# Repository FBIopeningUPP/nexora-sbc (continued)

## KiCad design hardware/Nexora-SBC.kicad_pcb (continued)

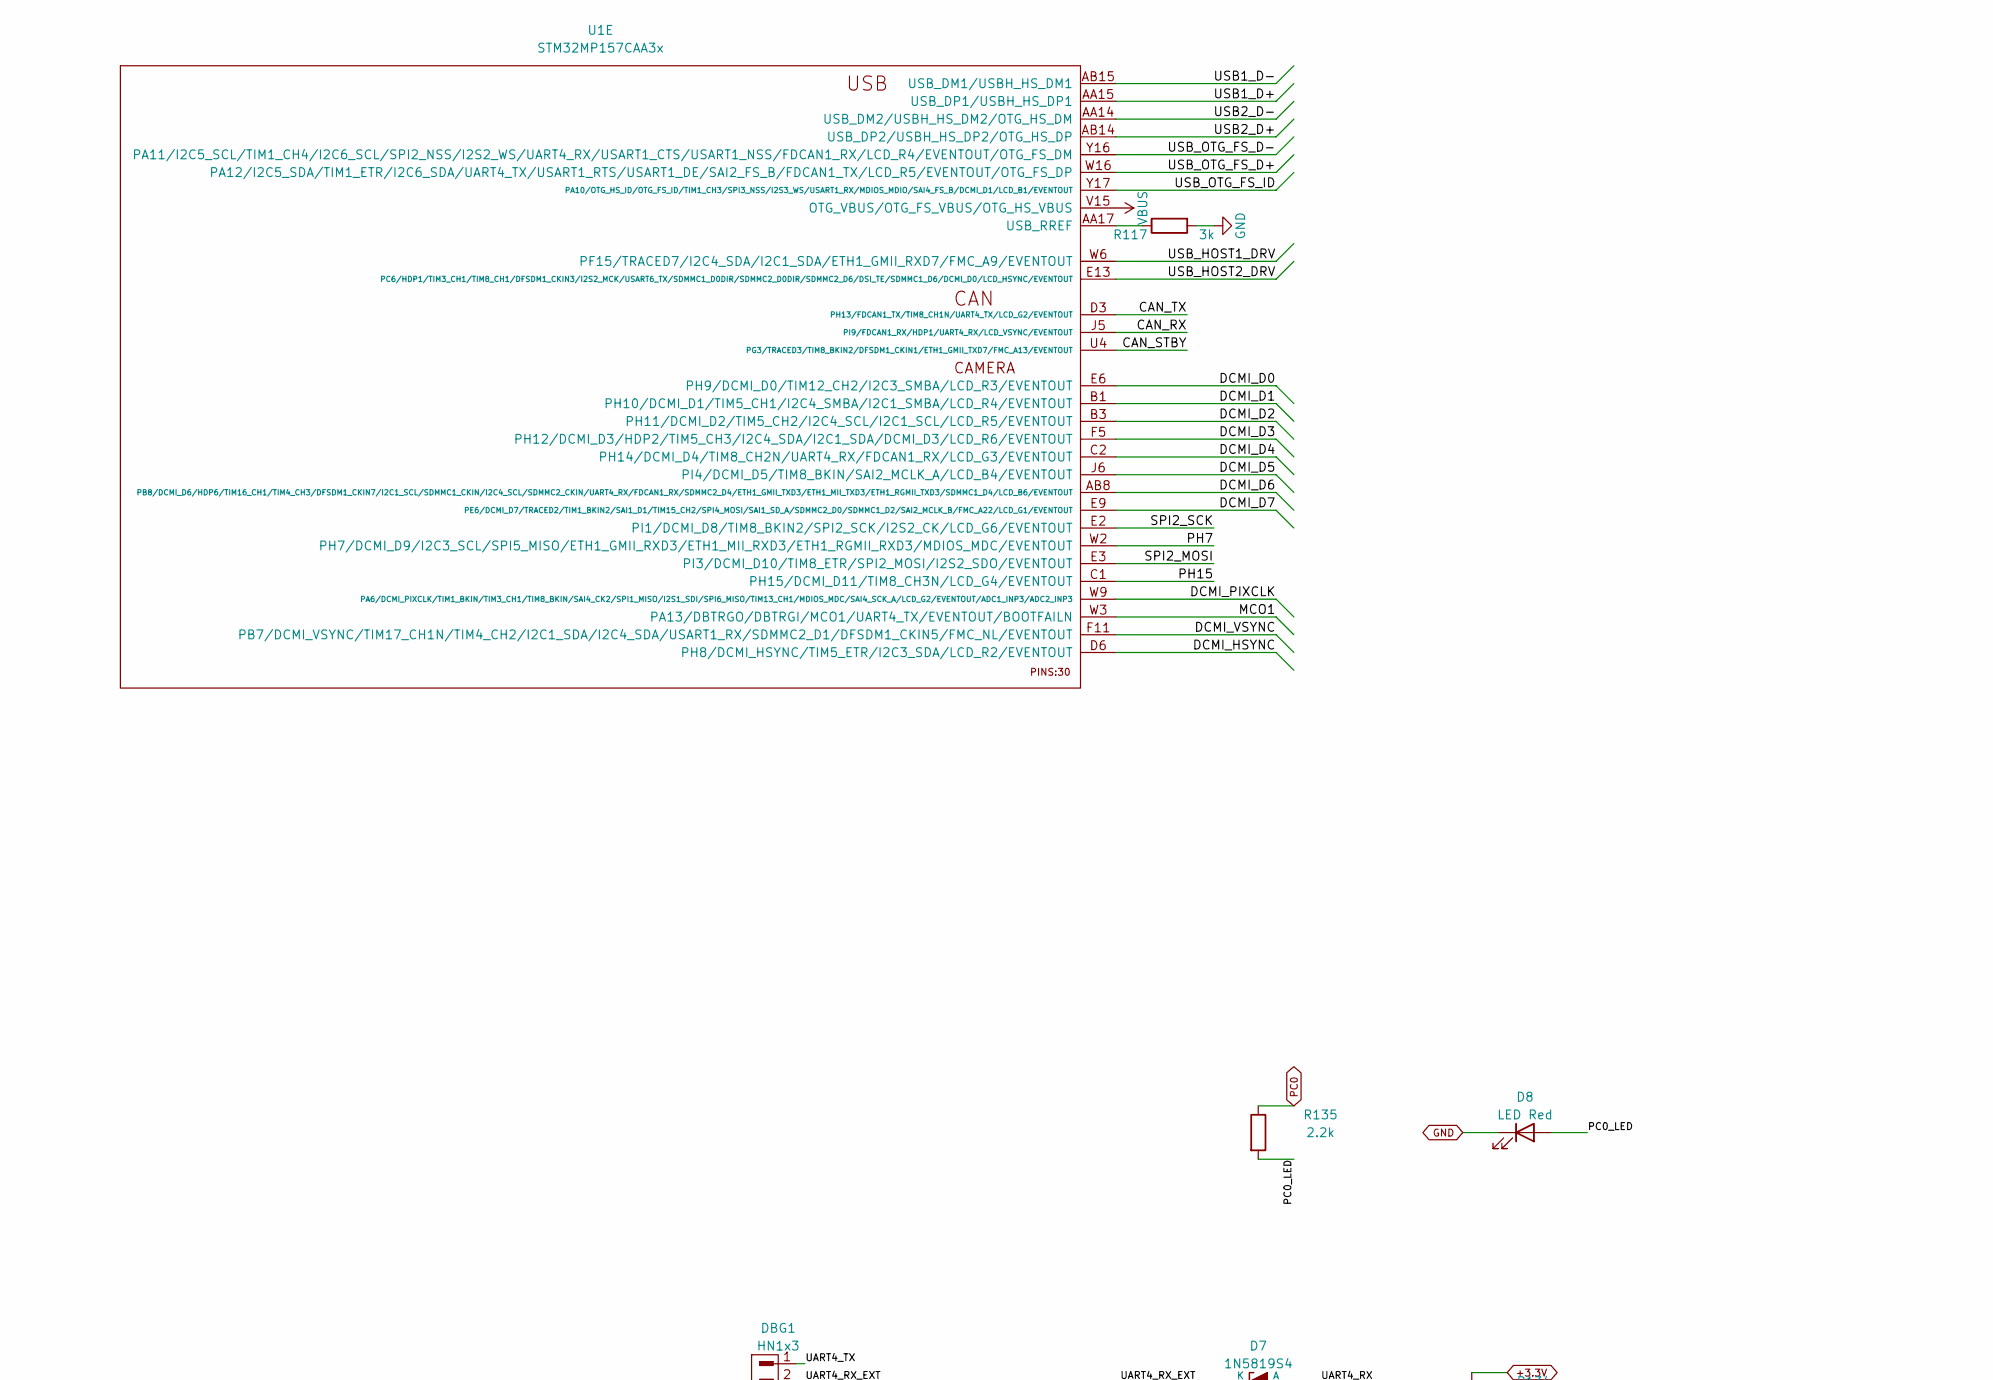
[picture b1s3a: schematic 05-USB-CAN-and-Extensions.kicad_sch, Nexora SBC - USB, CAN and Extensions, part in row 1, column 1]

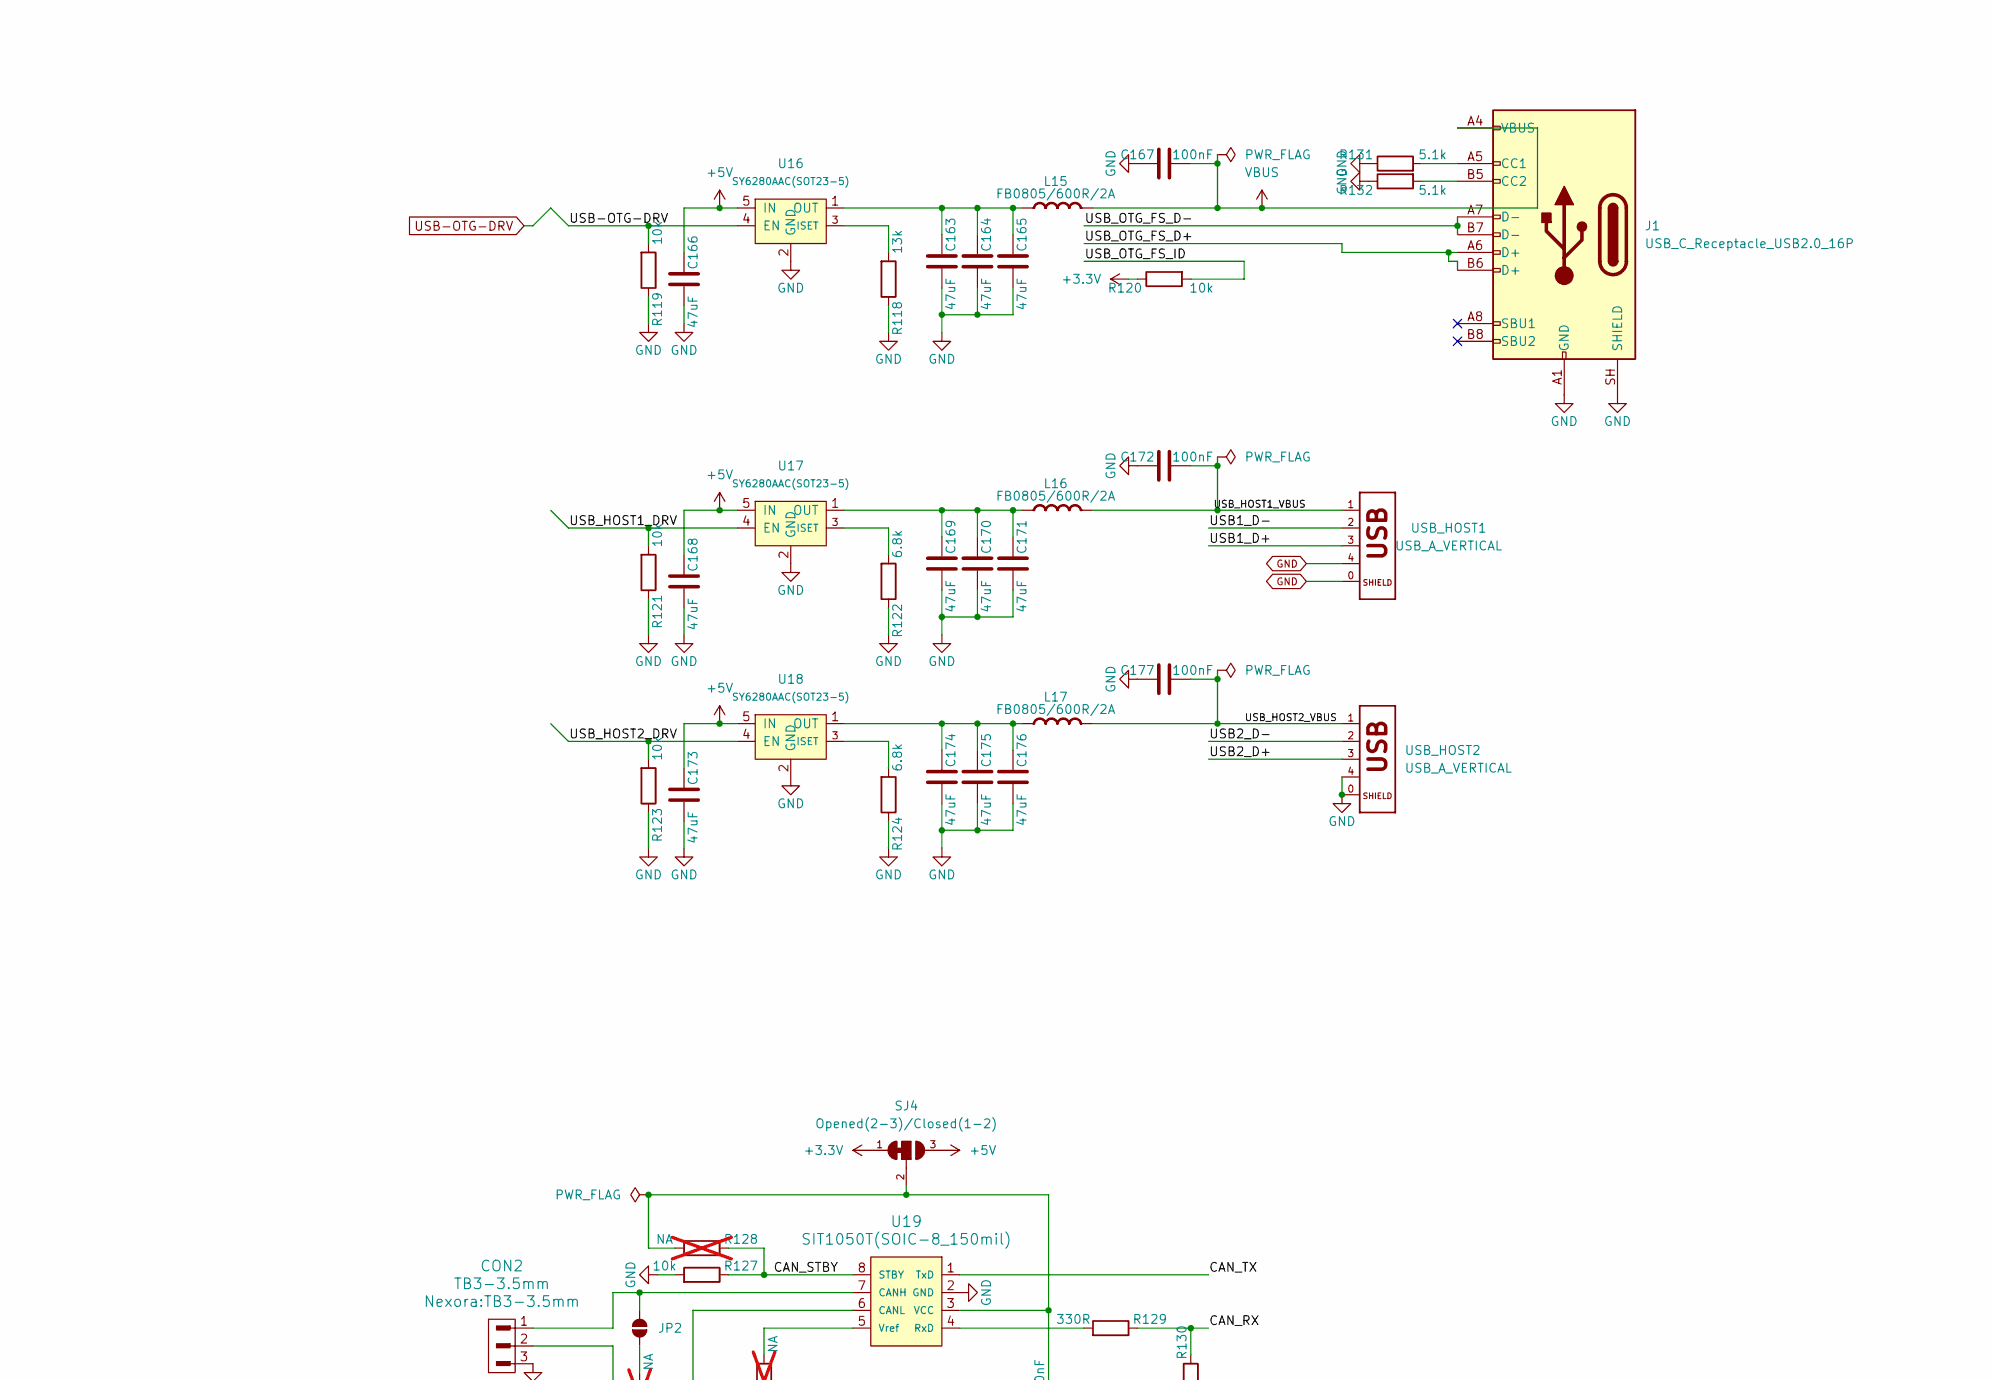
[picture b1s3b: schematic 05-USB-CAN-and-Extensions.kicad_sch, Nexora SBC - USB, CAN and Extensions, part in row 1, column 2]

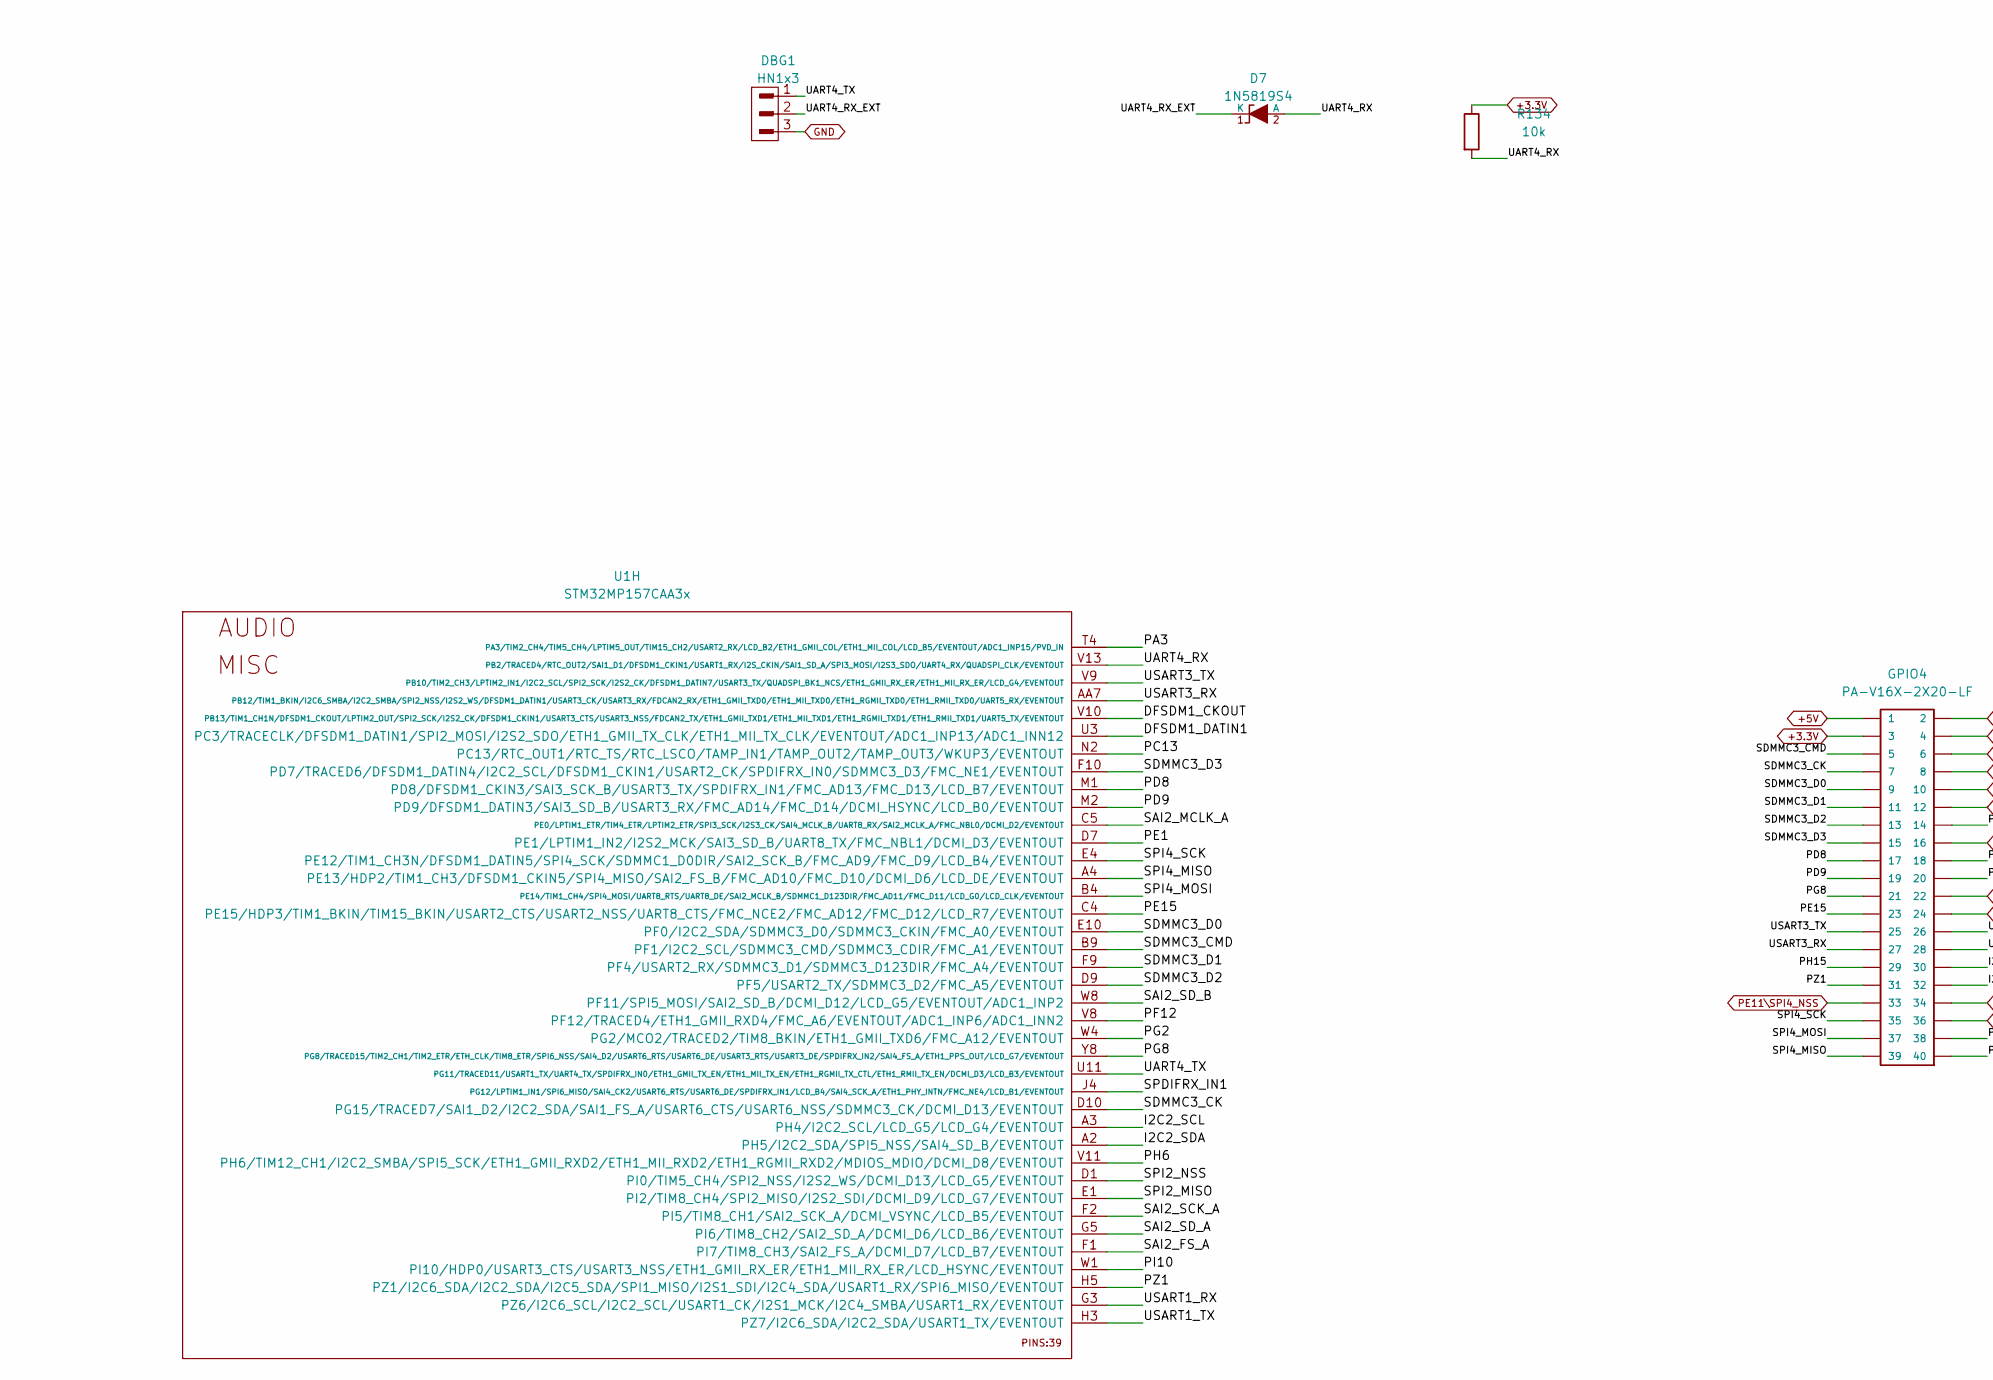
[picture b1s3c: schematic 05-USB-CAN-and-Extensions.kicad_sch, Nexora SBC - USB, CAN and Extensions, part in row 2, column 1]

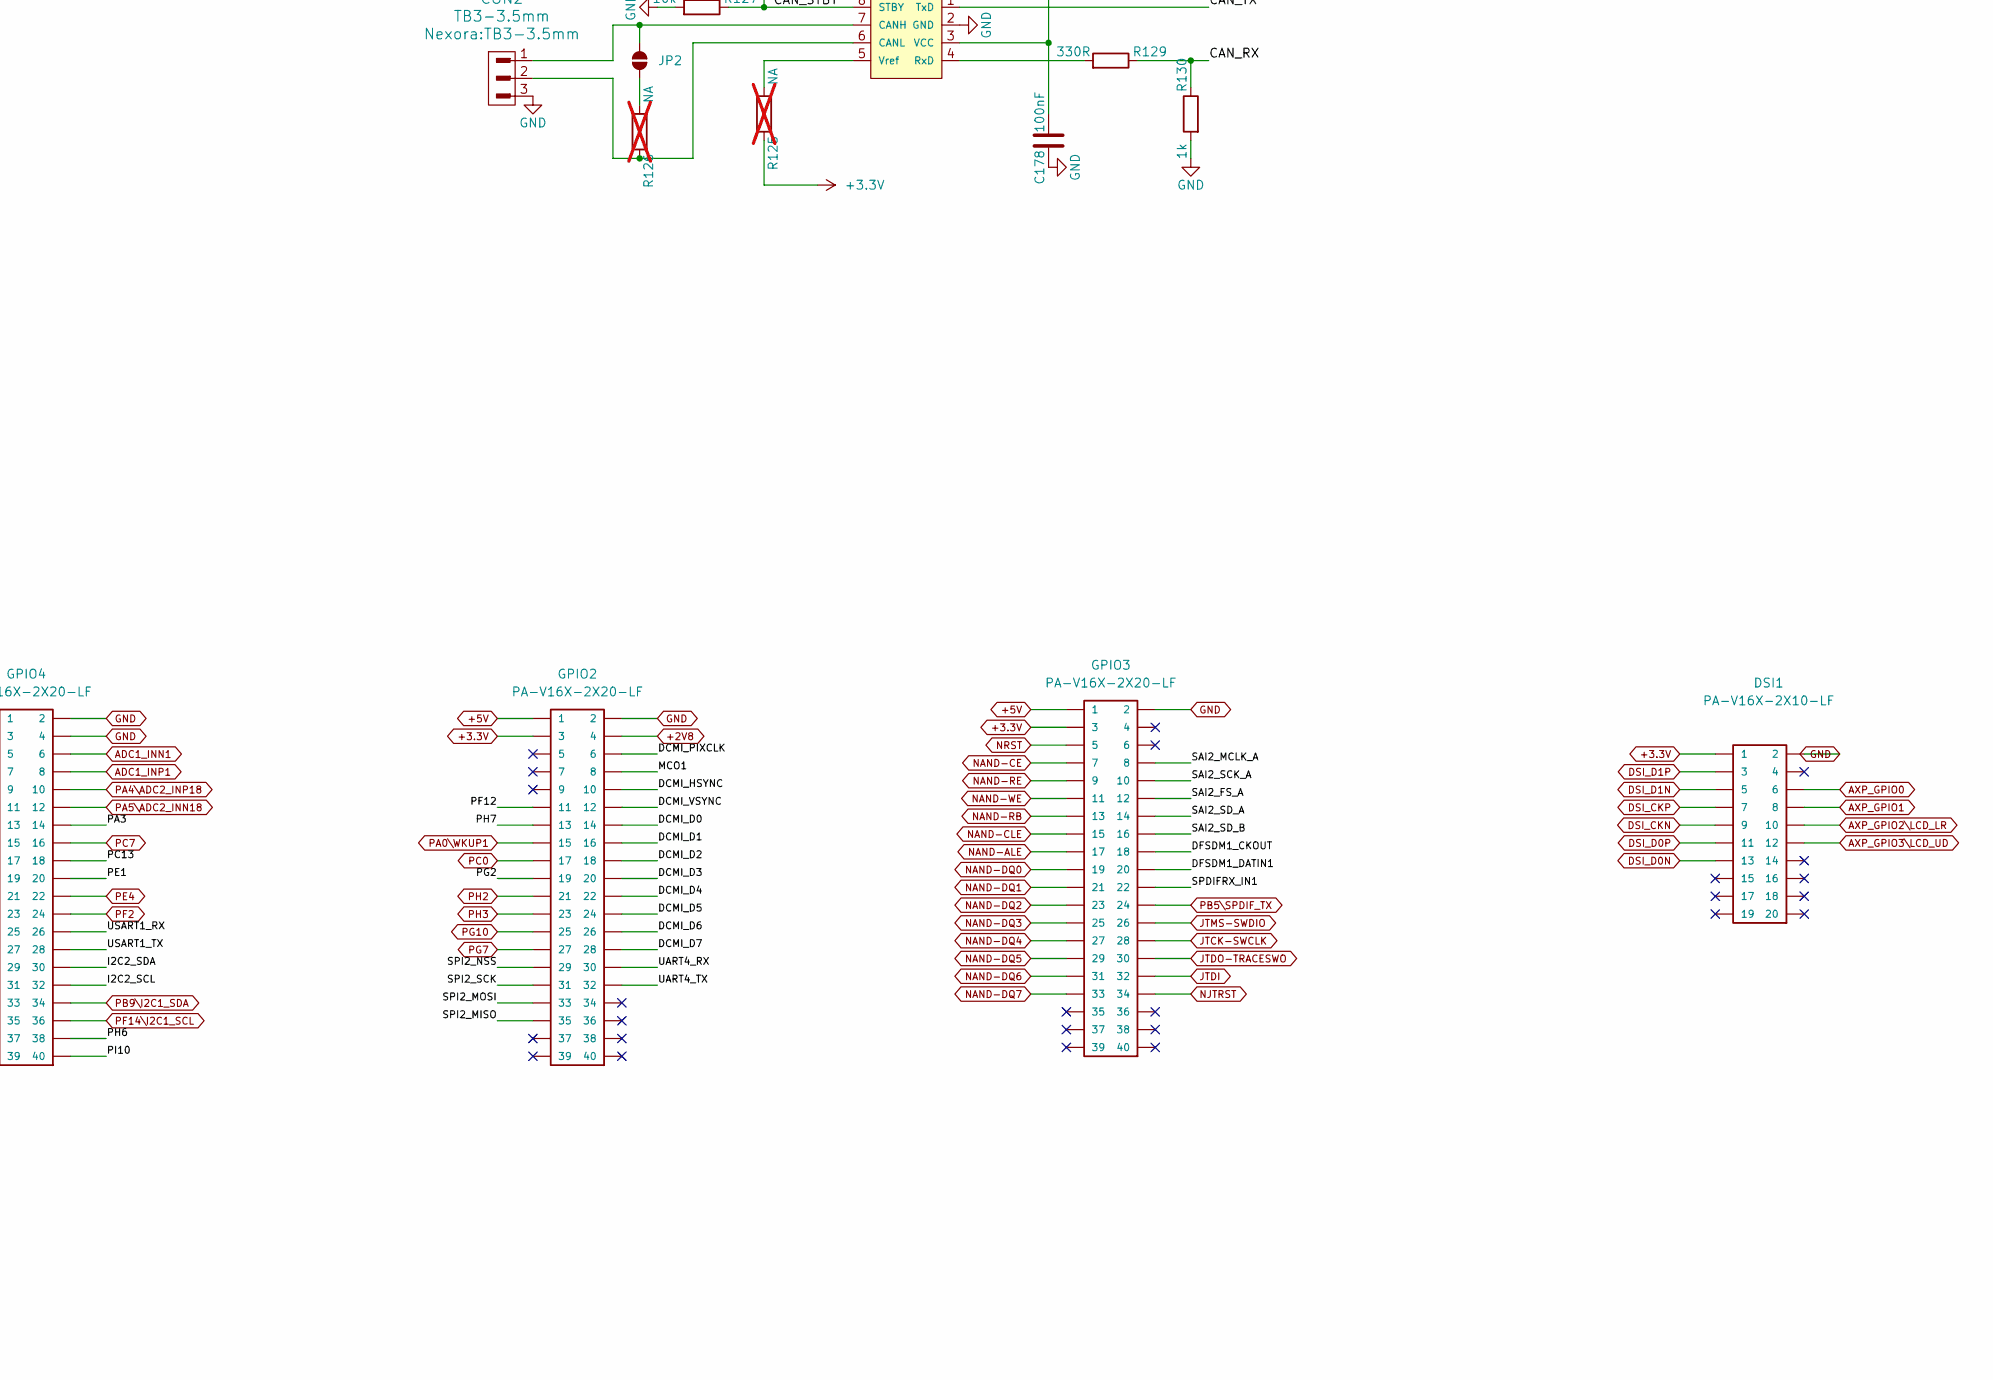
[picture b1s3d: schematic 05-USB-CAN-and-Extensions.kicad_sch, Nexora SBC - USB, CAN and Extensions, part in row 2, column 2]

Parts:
C163, C164, C165, C166, C168, C169, C170, C171, C173, C174, C175, C176: 47uF; C_0402_1005Metric
C167, C172, C177, C178: 100nF; C_0402_1005Metric
CON2: TB3-3.5mm
D7: 1N5819S4; D_SOD-123
D8: LED Red; LED_0603_1608Metric
DBG1: HN1x3
DSI1: PA-V16X-2X10-LF; GPH127SMT-02X10(PA-V16X-2X10-LF)
GPIO2, GPIO3, GPIO4: PA-V16X-2X20-LF; GPH127SMT-02X20(PA-V16X-2X20-LF)
J1: USB_C_Receptacle_USB2.0_16P; USB_C_Receptacle_G-Switch_GT-USB-7010ASV
JP2: Jumper_2_NO
L15, L16, L17: FB0805/600R/2A; L_0805_2012Metric; Rating A
R117: 3k; R_0402_1005Metric
R118: 13k; R_0402_1005Metric
R119, R120, R121, R123, R127, R134: 10k; R_0402_1005Metric
R122, R124: 6.8k; R_0402_1005Metric
R125, R126, R128: NA; R_0402_1005Metric; not fitted
R129: 330R; R_0402_1005Metric
R130: 1k; R_0402_1005Metric
R131, R132: 5.1k; R_0402_1005Metric
R135: 2.2k; R_0402_1005Metric
SJ4: Opened(2-3)/Closed(1-2); SJ_2_SMALL_12_TIED
U1: STM32MP157CAA3x; LFBGA-448(Pitch-0.8mm_Pad-0.4mm_18x18x1.27mm)
U16, U17, U18: SY6280AAC(SOT23-5); SOT-23-5
U19: SIT1050T(SOIC-8_150mil); SOIC-8_3.9x4.9mm_P1.27mm
USB_HOST1, USB_HOST2: USB_A_VERTICAL; USB_A_VERTICAL_PTH

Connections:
+2V8: GPIO2.4; also elsewhere on the board
+3.3V: DSI1.1, GPIO2.3, GPIO3.3, GPIO4.3, R120.2, R125.2, R134.1, SJ4.1; also elsewhere on the board
+5V: C166.1, C168.1, C173.1, GPIO2.1, GPIO3.1, GPIO4.1, SJ4.3, U16.5 (IN), U17.5 (IN), U18.5 (IN); also elsewhere on the board
/USB, CAN and Extensions/CAN_RX: R129.2, R130.2, U1.J5 (PI9/FDCAN1_RX/HDP1/UART4_RX/LCD_VSYNC/E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)
/USB, CAN and Extensions/CAN_STBY: R127.2, R128.2, U1.U4 (PG3/TRACED3/TIM8_BKIN2/DFSDM1_CKIN1/ETH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), U19.8 (STBY)
/USB, CAN and Extensions/CAN_TX: U1.D3 (PH13/FDCAN1_TX/TIM8_CH1N/UART4_TX/LCD_G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), U19.1 (TxD)
/USB, CAN and Extensions/DCMI_D0: GPIO2.14, U1.E6 (PH9/DCMI_D0/TIM12_CH2/I2C3_SMBA/LCD_R3/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)
/USB, CAN and Extensions/DCMI_D1: GPIO2.16, U1.B1 (PH10/DCMI_D1/TIM5_CH1/I2C4_SMBA/I2C1_SM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)
/USB, CAN and Extensions/DCMI_D2: GPIO2.18, U1.B3 (PH11/DCMI_D2/TIM5_CH2/I2C4_SCL/I2C1_SCL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)
/USB, CAN and Extensions/DCMI_D3: GPIO2.20, U1.F5 (PH12/DCMI_D3/HDP2/TIM5_CH3/I2C4_SDA/I2C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)
/USB, CAN and Extensions/DCMI_D4: GPIO2.22, U1.C2 (PH14/DCMI_D4/TIM8_CH2N/UART4_RX/FDCAN1_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)
/USB, CAN and Extensions/DCMI_D5: GPIO2.24, U1.J6 (PI4/DCMI_D5/TIM8_BKIN/SAI2_MCLK_A/LCD_B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)
/USB, CAN and Extensions/DCMI_D6: GPIO2.26, U1.AB8 (PB8/DCMI_D6/HDP6/TIM16_CH1/TIM4_CH3/DFS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)
/USB, CAN and Extensions/DCMI_D7: GPIO2.28, U1.E9 (PE6/DCMI_D7/TRACED2/TIM1_BKIN2/SAI1_D1/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)
/USB, CAN and Extensions/DCMI_HSYNC: GPIO2.10, U1.D6 (PH8/DCMI_HSYNC/TIM5_ETR/I2C3_SDA/LCD_R2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)
/USB, CAN and Extensions/DCMI_PIXCLK: GPIO2.6, U1.W9 (PA6/DCMI_PIXCLK/TIM1_BKIN/TIM3_CH1/TIM8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)
/USB, CAN and Extensions/DCMI_VSYNC: GPIO2.12, U1.F11 (PB7/DCMI_VSYNC/TIM17_CH1N/TIM4_CH2/I2C1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)
/USB, CAN and Extensions/DFSDM1_CKOUT: GPIO3.18, U1.V10 (PB13/TIM1_CH1N/DFSDM1_CKOUT/LPTIM2_OUT/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)
/USB, CAN and Extensions/DFSDM1_DATIN1: GPIO3.20, U1.U3 (PC3/TRACECLK/DFSDM1_DATIN1/SPI2_MOSI/I2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)
/USB, CAN and Extensions/I2C2_SCL: GPIO4.32, U1.A3 (PH4/I2C2_SCL/LCD_G5/LCD_G4/EVENTOUT)
/USB, CAN and Extensions/I2C2_SDA: GPIO4.30, U1.A2 (PH5/I2C2_SDA/SPI5_NSS/SAI4_SD_B/EVENTOUT)
/USB, CAN and Extensions/MCO1: GPIO2.8, U1.W3 (PA13/DBTRGO/DBTRGI/MCO1/UART4_TX/EVENTO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)
/USB, CAN and Extensions/PA3: GPIO4.14, U1.T4 (PA3/TIM2_CH4/TIM5_CH4/LPTIM5_OUT/TIM15_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)
/USB, CAN and Extensions/PC0_LED: D8.2 (A), R135.2
/USB, CAN and Extensions/PC13: GPIO4.18, U1.N2 (PC13/RTC_OUT1/RTC_TS/RTC_LSCO/TAMP_IN1/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)
/USB, CAN and Extensions/PD8: GPIO4.17, U1.M1 (PD8/DFSDM1_CKIN3/SAI3_SCK_B/USART3_TX/S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)
/USB, CAN and Extensions/PD9: GPIO4.19, U1.M2 (PD9/DFSDM1_DATIN3/SAI3_SD_B/USART3_RX/F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)
/USB, CAN and Extensions/PE1: GPIO4.20, U1.D7 (PE1/LPTIM1_IN2/I2S2_MCK/SAI3_SD_B/UART8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)
/USB, CAN and Extensions/PE15: GPIO4.23, U1.C4 (PE15/HDP3/TIM1_BKIN/TIM15_BKIN/USART2_C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)
/USB, CAN and Extensions/PF12: GPIO2.11, U1.V8 (PF12/TRACED4/ETH1_GMII_RXD4/FMC_A6/EVEN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)
/USB, CAN and Extensions/PG2: GPIO2.19, U1.W4 (PG2/MCO2/TRACED2/TIM8_BKIN/ETH1_GMII_TX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)
/USB, CAN and Extensions/PG8: GPIO4.21, U1.Y8 (PG8/TRACED15/TIM2_CH1/TIM2_ETR/ETH_CLK/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)
/USB, CAN and Extensions/PH6: GPIO4.38, U1.V11 (PH6/TIM12_CH1/I2C2_SMBA/SPI5_SCK/ETH1_G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)
/USB, CAN and Extensions/PH7: GPIO2.13, U1.W2 (PH7/DCMI_D9/I2C3_SCL/SPI5_MISO/ETH1_GMI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)
/USB, CAN and Extensions/PH15: GPIO4.29, U1.C1 (PH15/DCMI_D11/TIM8_CH3N/LCD_G4/EVENTOUT)
/USB, CAN and Extensions/PI10: GPIO4.40, U1.W1 (PI10/HDP0/USART3_CTS/USART3_NSS/ETH1_GM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)
/USB, CAN and Extensions/PZ1: GPIO4.31, U1.H5 (PZ1/I2C6_SDA/I2C2_SDA/I2C5_SDA/SPI1_MIS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)
/USB, CAN and Extensions/SAI2_FS_A: GPIO3.12, U1.F1 (PI7/TIM8_CH3/SAI2_FS_A/DCMI_D7/LCD_B7/E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)
/USB, CAN and Extensions/SAI2_MCLK_A: GPIO3.8, U1.C5 (PE0/LPTIM1_ETR/TIM4_ETR/LPTIM2_ETR/SPI3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)
/USB, CAN and Extensions/SAI2_SCK_A: GPIO3.10, U1.F2 (PI5/TIM8_CH1/SAI2_SCK_A/DCMI_VSYNC/LCD_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)
/USB, CAN and Extensions/SAI2_SD_A: GPIO3.14, U1.G5 (PI6/TIM8_CH2/SAI2_SD_A/DCMI_D6/LCD_B6/E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)
/USB, CAN and Extensions/SAI2_SD_B: GPIO3.16, U1.W8 (PF11/SPI5_MOSI/SAI2_SD_B/DCMI_D12/LCD_G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)
/USB, CAN and Extensions/SDMMC3_CK: GPIO4.7, U1.D10 (PG15/TRACED7/SAI1_D2/I2C2_SDA/SAI1_FS_A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)
/USB, CAN and Extensions/SDMMC3_CMD: GPIO4.5, U1.B9 (PF1/I2C2_SCL/SDMMC3_CMD/SDMMC3_CDIR/FMC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)
/USB, CAN and Extensions/SDMMC3_D0: GPIO4.9, U1.E10 (PF0/I2C2_SDA/SDMMC3_D0/SDMMC3_CKIN/FMC_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)
/USB, CAN and Extensions/SDMMC3_D1: GPIO4.11, U1.F9 (PF4/USART2_RX/SDMMC3_D1/SDMMC3_D123DIR/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)
/USB, CAN and Extensions/SDMMC3_D2: GPIO4.13, U1.D9 (PF5/USART2_TX/SDMMC3_D2/FMC_A5/EVENTOUT)
/USB, CAN and Extensions/SDMMC3_D3: GPIO4.15, U1.F10 (PD7/TRACED6/DFSDM1_DATIN4/I2C2_SCL/DFSD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)
/USB, CAN and Extensions/SPDIFRX_IN1: GPIO3.22, U1.J4 (PG12/LPTIM1_IN1/SPI6_MISO/SAI4_CK2/USAR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)
/USB, CAN and Extensions/SPI2_MISO: GPIO2.35, U1.E1 (PI2/TIM8_CH4/SPI2_MISO/I2S2_SDI/DCMI_D9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)
/USB, CAN and Extensions/SPI2_MOSI: GPIO2.33, U1.E3 (PI3/DCMI_D10/TIM8_ETR/SPI2_MOSI/I2S2_SD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)
/USB, CAN and Extensions/SPI2_NSS: GPIO2.29, U1.D1 (PI0/TIM5_CH4/SPI2_NSS/I2S2_WS/DCMI_D13/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)
/USB, CAN and Extensions/SPI2_SCK: GPIO2.31, U1.E2 (PI1/DCMI_D8/TIM8_BKIN2/SPI2_SCK/I2S2_CK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)
/USB, CAN and Extensions/SPI4_MISO: GPIO4.39, U1.A4 (PE13/HDP2/TIM1_CH3/DFSDM1_CKIN5/SPI4_MI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)
/USB, CAN and Extensions/SPI4_MOSI: GPIO4.37, U1.B4 (PE14/TIM1_CH4/SPI4_MOSI/UART8_RTS/UART8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)
/USB, CAN and Extensions/SPI4_SCK: GPIO4.35, U1.E4 (PE12/TIM1_CH3N/DFSDM1_DATIN5/SPI4_SCK/S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)
/USB, CAN and Extensions/UART4_RX: D7.2 (A), GPIO2.30, R134.2, U1.V13 (PB2/TRACED4/RTC_OUT2/SAI1_D1/DFSDM1_CKI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)
/USB, CAN and Extensions/UART4_RX_EXT: D7.1 (K), DBG1.2
/USB, CAN and Extensions/UART4_TX: DBG1.1, GPIO2.32, U1.U11 (PG11/TRACED11/USART1_TX/UART4_TX/SPDIFR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)
/USB, CAN and Extensions/USART1_RX: GPIO4.26, U1.G3 (PZ6/I2C6_SCL/I2C2_SCL/USART1_CK/I2S1_MC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)
/USB, CAN and Extensions/USART1_TX: GPIO4.28, U1.H3 (PZ7/I2C6_SDA/I2C2_SDA/USART1_TX/EVENTOUT)
/USB, CAN and Extensions/USART3_RX: GPIO4.27, U1.AA7 (PB12/TIM1_BKIN/I2C6_SMBA/I2C2_SMBA/SPI2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)
/USB, CAN and Extensions/USART3_TX: GPIO4.25, U1.V9 (PB10/TIM2_CH3/LPTIM2_IN1/I2C2_SCL/SPI2_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)
/USB, CAN and Extensions/USB1_D+: U1.AA15 (USB_DP1/USBH_HS_DP1), USB_HOST1.3
/USB, CAN and Extensions/USB1_D-: U1.AB15 (USB_DM1/USBH_HS_DM1), USB_HOST1.2
/USB, CAN and Extensions/USB2_D+: U1.AB14 (USB_DP2/USBH_HS_DP2/OTG_HS_DP), USB_HOST2.3
/USB, CAN and Extensions/USB2_D-: U1.AA14 (USB_DM2/USBH_HS_DM2/OTG_HS_DM), USB_HOST2.2
/USB, CAN and Extensions/USB_HOST1_DRV: R121.1, U1.W6 (PF15/TRACED7/I2C4_SDA/I2C1_SDA/ETH1_GMI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), U17.4 (EN)
/USB, CAN and Extensions/USB_HOST1_VBUS: C172.2, L16.2 (-), USB_HOST1.1
/USB, CAN and Extensions/USB_HOST2_DRV: R123.1, U1.E13 (PC6/HDP1/TIM3_CH1/TIM8_CH1/DFSDM1_CKIN3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), U18.4 (EN)
/USB, CAN and Extensions/USB_HOST2_VBUS: C177.2, L17.2 (-), USB_HOST2.1
/USB, CAN and Extensions/USB_OTG_FS_D+: J1.A6 (D+), J1.B6 (D+), U1.W16 (PA12/I2C5_SDA/TIM1_ETR/I2C6_SDA/UART4_T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)
/USB, CAN and Extensions/USB_OTG_FS_D-: J1.A7 (D-), J1.B7 (D-), U1.Y16 (PA11/I2C5_SCL/TIM1_CH4/I2C6_SCL/SPI2_NS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)
/USB, CAN and Extensions/USB_OTG_FS_ID: R120.1, U1.Y17 (PA10/OTG_HS_ID/OTG_FS_ID/TIM1_CH3/SPI3_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)
ADC1_INN1: GPIO4.6; also elsewhere on the board
ADC1_INP1: GPIO4.8; also elsewhere on the board
AXP_GPIO0: DSI1.6; also elsewhere on the board
AXP_GPIO1: DSI1.8; also elsewhere on the board
AXP_GPIO2\LCD_LR: DSI1.10; also elsewhere on the board
AXP_GPIO3\LCD_UD: DSI1.12; also elsewhere on the board
DSI_CKN: DSI1.9; also elsewhere on the board
DSI_CKP: DSI1.7; also elsewhere on the board
DSI_D0N: DSI1.13; also elsewhere on the board
DSI_D0P: DSI1.11; also elsewhere on the board
DSI_D1N: DSI1.5; also elsewhere on the board
DSI_D1P: DSI1.3; also elsewhere on the board
GND: C163.2, C164.2, C165.2, C166.2, C167.1, C168.2, C169.2, C170.2, C171.2, C172.1, C173.2, C174.2, C175.2, C176.2, C177.1, C178.1, CON2.3, D8.1 (K), DBG1.3, DSI1.2, GPIO2.2, GPIO3.2, GPIO4.2, GPIO4.4, J1.A1 (GND), J1.A12 (GND), J1.B1 (GND), J1.B12 (GND), J1.SH (SHIELD), R117.1, R118.2, R119.2, R121.2, R122.2, R123.2, R124.2, R127.1, R130.1, R131.2, R132.2, U16.2 (GND), U17.2 (GND), U18.2 (GND), U19.2 (GND), USB_HOST1.0 (5), USB_HOST1.4, USB_HOST2.0 (5), USB_HOST2.4; also elsewhere on the board
JTCK-SWCLK: GPIO3.28; also elsewhere on the board
JTDI: GPIO3.32; also elsewhere on the board
JTDO-TRACESWO: GPIO3.30; also elsewhere on the board
JTMS-SWDIO: GPIO3.26; also elsewhere on the board
NAND-ALE: GPIO3.17; also elsewhere on the board
NAND-CE: GPIO3.7; also elsewhere on the board
NAND-CLE: GPIO3.15; also elsewhere on the board
NAND-DQ0: GPIO3.19; also elsewhere on the board
NAND-DQ1: GPIO3.21; also elsewhere on the board
NAND-DQ2: GPIO3.23; also elsewhere on the board
NAND-DQ3: GPIO3.25; also elsewhere on the board
NAND-DQ4: GPIO3.27; also elsewhere on the board
NAND-DQ5: GPIO3.29; also elsewhere on the board
NAND-DQ6: GPIO3.31; also elsewhere on the board
NAND-DQ7: GPIO3.33; also elsewhere on the board
NAND-RB: GPIO3.13; also elsewhere on the board
NAND-RE: GPIO3.9; also elsewhere on the board
NAND-WE: GPIO3.11; also elsewhere on the board
NJTRST: GPIO3.34; also elsewhere on the board
NRST: GPIO3.5; also elsewhere on the board
unnamed: J1.A5 (CC1), R131.1
unnamed: J1.B5 (CC2), R132.1
unnamed: JP2.1 (A), R126.1
unnamed: CON2.1, JP2.2 (B), U19.7 (CANH)
unnamed: C163.1, C164.1, C165.1, L15.1 (+), U16.1 (OUT)
unnamed: C169.1, C170.1, C171.1, L16.1 (+), U17.1 (OUT)
unnamed: C174.1, C175.1, C176.1, L17.1 (+), U18.1 (OUT)
unnamed: R117.2, U1.AA17 (USB_RREF)
unnamed: R118.1, U16.3 (ISET)
unnamed: R122.1, U17.3 (ISET)
unnamed: R124.1, U18.3 (ISET)
unnamed: CON2.2, R126.2, U19.6 (CANL)
unnamed: R129.1, U19.4 (RxD)
unnamed: C178.2, R128.1, SJ4.2, U19.3 (VCC)
unnamed: R125.1, U19.5 (Vref)
PA0\WKUP1: GPIO2.15; also elsewhere on the board
PA4\ADC2_INP18: GPIO4.10; also elsewhere on the board
PA5\ADC2_INN18: GPIO4.12; also elsewhere on the board
PB5\SPDIF_TX: GPIO3.24; also elsewhere on the board
PB9\I2C1_SDA: GPIO4.34; also elsewhere on the board
PC0: GPIO2.17, R135.1; also elsewhere on the board
PC7: GPIO4.16; also elsewhere on the board
PE4: GPIO4.22; also elsewhere on the board
PE11\SPI4_NSS: GPIO4.33; also elsewhere on the board
PF2: GPIO4.24; also elsewhere on the board
PF14\I2C1_SCL: GPIO4.36; also elsewhere on the board
PG7: GPIO2.27; also elsewhere on the board
PG10: GPIO2.25; also elsewhere on the board
PH2: GPIO2.21; also elsewhere on the board
PH3: GPIO2.23; also elsewhere on the board
USB-OTG-DRV: R119.1, U16.4 (EN); also elsewhere on the board
VBUS: C167.2, J1.A4 (VBUS), J1.A9 (VBUS), J1.B4 (VBUS), J1.B9 (VBUS), L15.2 (-), U1.V15 (OTG_VBUS/OTG_FS_VBUS/OTG_HS_VBUS); also elsewhere on the board
